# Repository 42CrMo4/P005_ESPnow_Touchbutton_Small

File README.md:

# KiCad_Template

This is a template repo for KiCAD v6 projects with 

## Todo

* ~add DRC, ERC as seperate WF~ 
* ~add DRC, ERC to release WF as blocking~
* ~add release checklist~
* order release checklist
* ~add workflow to automatically create new realease checklist and realease note file and reset the generic for the next release~
* ~Rename artefacts with project name and date?~
* Add diffrent PCB manufactures output via kibot
* ~Update to kicad6_auto:1.3.0~
* use version number for template

## Usage

hit "use this template" button
delet all unneded files in Doc folder
delet all Schematic stuff but not the text Placeholders <<...>>
delet all PCB stuff but not the text Placeholders <<...>> and the Board Edge (or the iBOM will fail). You can remodel it later.

### Workflow
If not working:
setting -> action -> general -> Workflow permissions -> Read and write permissions

## working

in the first workflow run the action will create a new branch "documentation" to store the newest PCBdraw pictures. 
Each action run will force push the png to this branch. So so not use the Fabrication folder in the documentation branch.

## Description. 

| Font                                                                    | Back                                                                      |
|-------------------------------------------------------------------------|---------------------------------------------------------------------------|
|  |  |

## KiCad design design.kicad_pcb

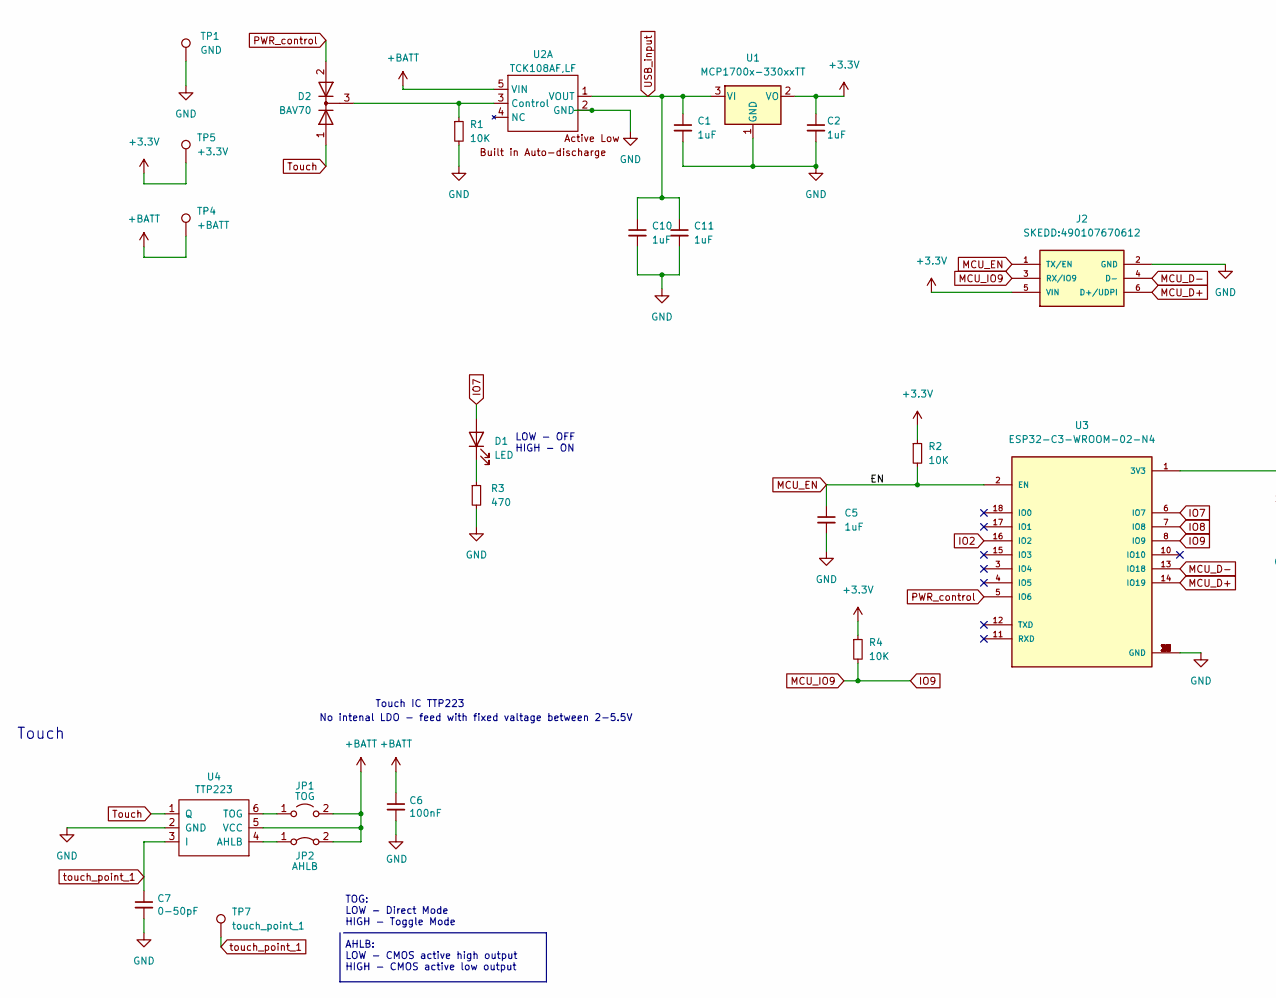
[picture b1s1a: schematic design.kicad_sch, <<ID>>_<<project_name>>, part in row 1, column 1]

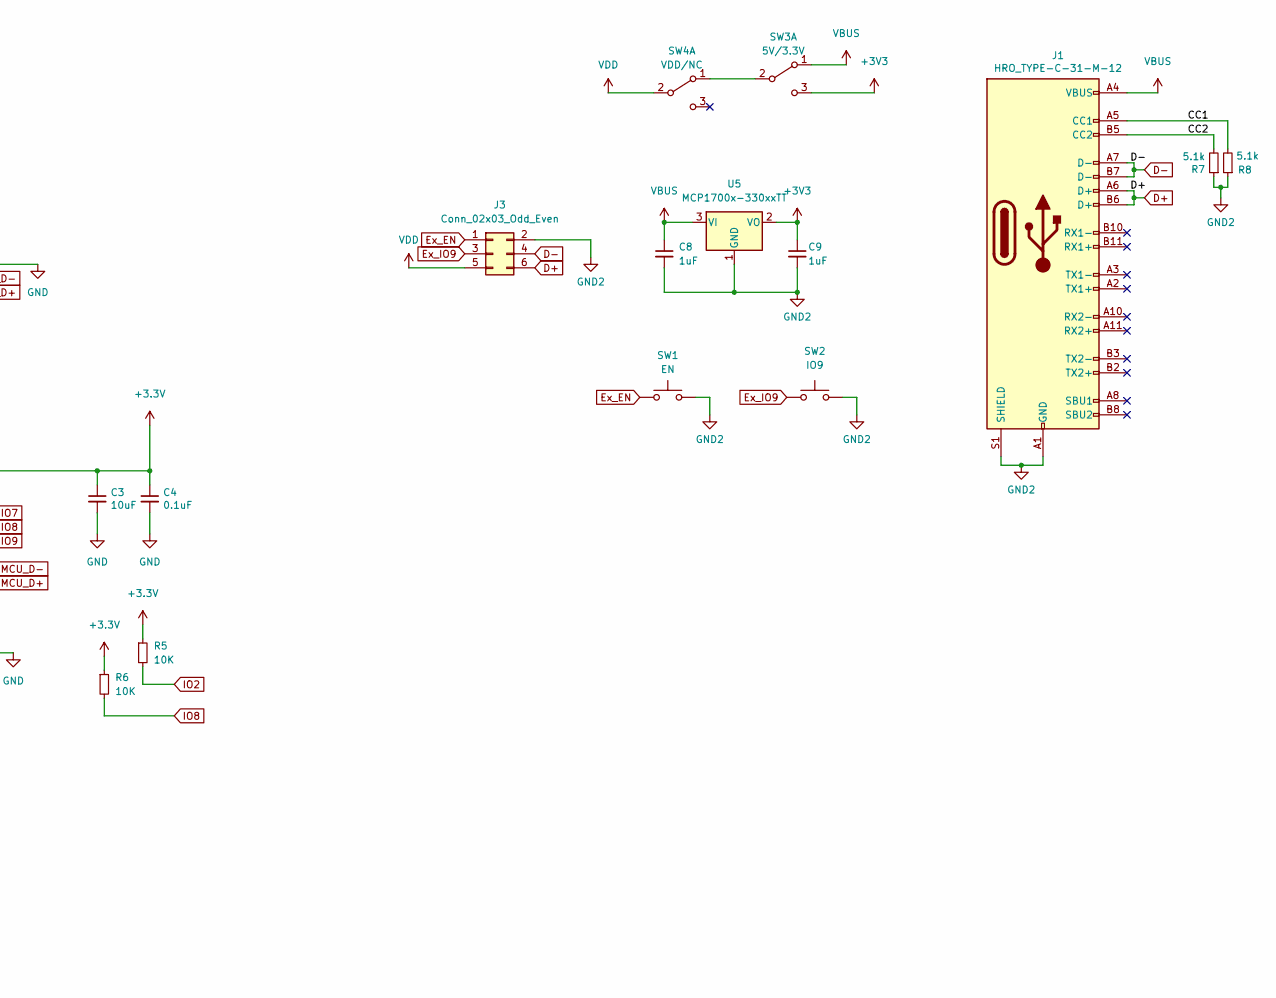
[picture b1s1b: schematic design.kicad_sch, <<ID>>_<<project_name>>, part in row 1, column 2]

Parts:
C1, C2, C5, C8, C9, C10, C11: 1uF; C_0805_2012Metric
C3: 10uF; C_0805_2012Metric
C4: 0.1uF; C_0805_2012Metric
C6: 100nF; C_0805_2012Metric
C7: 0-50pF; C_0805_2012Metric
D1: LED; LED_0603_1608Metric
D2: BAV70; SOT-23
J1: HRO_TYPE-C-31-M-12; USB_C_Receptacle_HRO_TYPE-C-31-M-12
J2: SKEDD:490107670612; WURTH_490107670612; PARTREV 002.003
J3: Conn_02x03_Odd_Even; PinHeader_2x03_P2.54mm_Vertical
JP1: TOG; SolderJumper-2_P1.3mm_Open_RoundedPad1.0x1.5mm
JP2: AHLB; SolderJumper-2_P1.3mm_Open_RoundedPad1.0x1.5mm
R1, R2, R4, R5, R6: 10K; R_0805_2012Metric
R3: 470; R_0805_2012Metric
R7, R8: 5.1k; R_0805_2012Metric
SW1: EN; RKB2
SW2: IO9; RKB2
SW3: 5V/3.3V; SW_DPDT_CK_JS202011JCQN
SW4: VDD/NC; SW_DPDT_CK_JS202011JCQN
TP1: GND; TestPoint_Pad_D2.5mm
TP4: +BATT; TestPoint_Pad_D2.5mm
TP5: +3.3V; TestPoint_Pad_D2.5mm
TP7: touch_point_1
U1, U5: MCP1700x-330xxTT; SOT-23
U2: TCK108AF,LF; SOT-23-5
U3: ESP32-C3-WROOM-02-N4; MODULE_ESP32-C3-WROOM-02-H4
U4: TTP223; SOT-23-6_Handsoldering

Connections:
+3.3V: C2.1, C3.1, C4.1, J2.5 (VIN), R2.1, R4.1, R5.1, R6.1, TP5.1, U1.2 (VO), U3.1 (3V3)
+3V3: C9.1, SW3.3 (C), U5.2 (VO)
+BATT: C6.1, JP1.2 (B), JP2.2 (B), TP4.1, U2.5 (VIN), U4.5 (VCC)
/CC1: J1.A5 (CC1), R8.2
/CC2: J1.B5 (CC2), R7.2
D+: J1.A6 (D+), J1.B6 (D+), J3.6
D-: J1.A7 (D-), J1.B7 (D-), J3.4
Ex_EN: J3.1, SW1.1
Ex_IO9: J3.3, SW2.1
GND: C1.2, C2.2, C3.2, C4.2, C5.2, C6.2, C7.2, C10.2, C11.2, J2.2 (GND), R1.2, R3.2, TP1.1, U1.1 (GND), U2.2 (GND), U3.9 (GND), U3.19 (GND), U3.20 (GND), U3.21 (GND), U3.22 (GND), U3.23 (GND), U3.24 (GND), U3.25 (GND), U3.26 (GND), U3.27 (GND), U3.28 (GND), U3.29 (GND), U3.30 (GND), U3.31 (GND), U3.32 (GND), U3.33 (GND), U3.34 (GND), U3.35 (GND), U3.36 (GND), U3.37 (GND), U3.38 (GND), U3.39 (GND), U4.2 (GND)
GND2: C8.2, C9.2, J1.A1 (GND), J1.A12 (GND), J1.B1 (GND), J1.B12 (GND), J1.S1 (SHIELD), J3.2, R7.1, R8.1, SW1.2, SW2.2, U5.1 (GND)
IO2: R5.2, U3.16 (IO2)
IO7: D1.2 (A), U3.6 (IO7)
IO8: R6.2, U3.7 (IO8)
IO9: J2.3 (RX/IO9), R4.2, U3.8 (IO9)
MCU_D+: J2.6 (D+/UDPI), U3.14 (IO19)
MCU_D-: J2.4 (D-), U3.13 (IO18)
MCU_EN: C5.1, J2.1 (TX/EN), R2.2, U3.2 (EN)
unnamed: D1.1 (K), R3.1
unnamed: JP1.1 (A), U4.6 (TOG)
unnamed: JP2.1 (A), U4.4 (AHLB)
unnamed: D2.3 (K), R1.1, U2.3 (Control)
unnamed: SW3.2 (B), SW4.1 (A)
PWR_control: D2.2 (A), U3.5 (IO6)
Touch: D2.1 (A), U4.1 (Q)
USB_input: C1.1, C10.1, C11.1, U1.3 (VI), U2.1 (VOUT)
VBUS: C8.1, J1.A4 (VBUS), J1.A9 (VBUS), J1.B4 (VBUS), J1.B9 (VBUS), SW3.1 (A), U5.3 (VI)
VDD: J3.5, SW4.2 (B)
touch_point_1: C7.1, TP7.1, U4.3 (I)

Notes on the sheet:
No intenal LDO - feed with fixed valtage between 2-5.5V
LOW - OFF HIGH - ON
Touch
TOG: LOW - Direct Mode HIGH - Toggle Mode AHLB: LOW - CMOS active high output HIGH - CMOS active low output
Touch IC TTP223

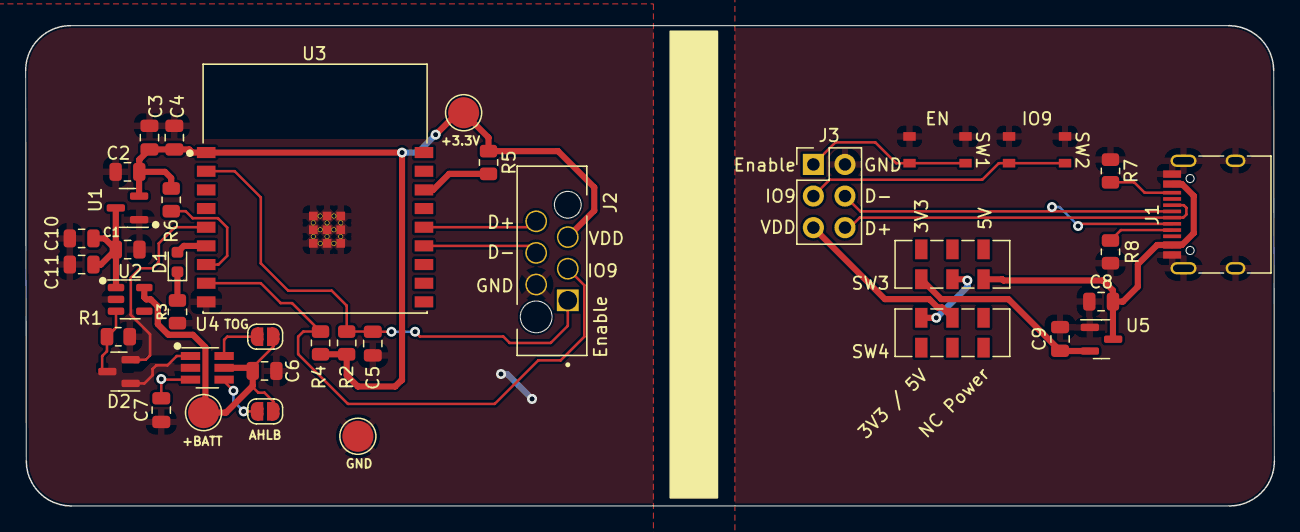
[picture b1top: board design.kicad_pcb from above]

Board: 2 copper layers, 100.4 x 38.6 mm, 38 parts (0 on the bottom side), 29 nets.

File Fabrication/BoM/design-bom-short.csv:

Row,Description,Part,References,Value,Footprint,Quantity Per PCB,Status,Datasheet,MF,AVAILABILITY,PRICE,PACKAGE,MP,PURCHASE-URL
1,"Unpolarized capacitor, small symbol",C_Small,C4 C6,0.1uF,C_0805_2012Metric,2, ,~,,,,,,
2,"Unpolarized capacitor, small symbol",C_Small,C1 C2 C5,1uF,C_0805_2012Metric,3, ,~,,,,,,
3,"Unpolarized capacitor, small symbol",C_Small,C3,10uF,C_0805_2012Metric,1, ,~,,,,,,
4,"Unpolarized capacitor, small symbol",C_Small,C7,0-50pF,C_0805_2012Metric,1, ,~,,,,,,
5,Light emitting diode,LED,D1,LED,LED_0603_1608Metric,1, ,~,,,,,,
6,USB 2.0-only Type-C Receptacle connector,USB4130-GF-C,J1,USB4130-GF-C,USB_C_Receptacle_GCT_USB4130-GF-C,1, ,https://gct.co/files/drawings/usb4130.pdf,,,,,,
7,"Jumper, 2-pole, closed/bridged",Jumper_2_Bridged,JP2,AHLB,SolderJumper-2_P1.3mm_Open_RoundedPad1.0x1.5mm,1, ,~,,,,,,
8,"Jumper, 2-pole, open",Jumper_2_Open,JP1,TOG,SolderJumper-2_P1.3mm_Open_RoundedPad1.0x1.5mm,1, ,~,,,,,,
9,"Resistor, small symbol",R_Small,R3,470,R_0805_2012Metric,1, ,~,,,,,,
10,"Resistor, small symbol",R_Small,R7 R8,5.1k,R_0805_2012Metric,2, ,~,,,,,,
11,"Resistor, small symbol",R_Small,R1 R2 R4 R5 R6,10K,R_0805_2012Metric,5, ,~,,,,,,
12,"Push button switch, generic, two pins",SW_Push,SW1,EN,SW_SPST_EVPBF,1, ,~,,,,,,
13,"Push button switch, generic, two pins",SW_Push,SW2,IO9,SW_SPST_EVPBF,1, ,~,,,,,,
14,"WiFi Modules (802.11) (Engineering Samples) SMD module, ESP32-C3, 4MB SPI flash, PCB antenna, -40 C +105 C",ESP32-C3-WROOM-02-N4,U3,ESP32-C3-WROOM-02-N4,MODULE_ESP32-C3-WROOM-02-H4,1, ,,Espressif Systems,In Stock,None,Package,ESP32-C3-WROOM-02-H4,https://pricing.snapeda.com/search/part/ESP32-C3-WROOM-02-H4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
15,"250mA Low Quiscent Current LDO, 3.3V output, SOT-23",MCP1700x-330xxTT,U1,MCP1700x-330xxTT,SOT-23,1, ,http://ww1.microchip.com/downloads/en/DeviceDoc/20001826D.pdf,,,,,,
16,,"TCK108AF,LF",U2,"TCK108AF,LF",SOT-23-5,1, ,https://toshiba.semicon-storage.com/info/TCK108AF_datasheet_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,,,,,,
17,,TTP223,U4,TTP223,SOT-23-6_Handsoldering,1, ,,,,,,,

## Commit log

2022-12-12 init
2022-12-12 Update Bom and PCB_top
2022-12-12 annotate + usb connector 3D
2022-12-12 remove unused 3d
2022-12-12 add 3d USB connector to project
2022-12-29 PCB&SCH update
2022-12-29 PCB design
2022-12-29 SCH handle all ERC error warnings
2022-12-29 Update 3Dview zoomlevel
2022-12-29 Add Project properties
2022-12-29 revise project name
2022-12-29 PCB pin 1 marker for u1
2022-12-29 PCB use circular mechanical USB holes
    so we can use cheaper manufacturing
2022-12-29 PCB fill zones
2022-12-29 PCB Add Project variable silkscreen in
2022-12-29 PCB Silkscreen Prj name
2022-12-29 Update Release note
2022-12-29 DEL old release notes/checklist from template
2022-12-29 PCB center Silkscreen
2022-12-29 Add Release Checklist
2022-12-29 Update Release Checklist
2022-12-29 WF pull latest template kibot.yml
2022-12-29 Archive & Renew release docs
2023-01-14 hatch 45x0.21x2x1x0.4
2023-01-14 hatch 45x0.21x3x1x0.4
2023-01-14 hatch 45x0.21x4x1x0.4
2023-01-14 hatch 45x0.21x5x1x0.4
2023-01-14 hatch 45x0.21x5x3x0.2 no keep out
2023-10-14 changes SCH PCB
2023-10-14 more update PCB SCH
2023-10-15 update to kibot 1.6.3 in generate output workflow
2023-10-15 put USB section own GND2 signal
2023-10-15 correct ERC problems
2023-10-15 resolve ERC
2023-10-15 put USB porgrammer in extra sheet
2023-10-15 remove _ in name
2023-10-15 make PCB smaller
2023-10-15 remove " " in name
2023-10-15 use a defined kicad_sch file
2023-10-15 Revert "use a defined kicad_sch file"
    This reverts commit 7166112afd66463a929f911f1df4588ada510726.
2023-10-15 Revert "Revert "use a defined kicad_sch file""
    This reverts commit d6faa50e60933f90e477d78ce633a047a2aa3bf2.
2023-10-15 revert subsheet in SCH
2023-10-15 do not specify a sheet
2023-10-15 Delete all to start from 4b65aec
    4b65aec3193d602a4a407a109111463c52960f84
2023-10-15 add all from 4b65aec
    4b65aec3193d602a4a407a109111463c52960f84
2023-10-15 modify Silkscreen
2023-10-15 make PCB smaller again
2023-10-15 add copper area on back to balance in production
2023-10-18 Add second Diode to Touch input
2023-10-27 change to tck 107 active high
